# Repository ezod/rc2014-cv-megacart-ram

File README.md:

# RC2014 ColecoVision MegaCart 32KB/512KB RAM Module

This is a RAM module for [RC2014](https://rc2014.co.uk/) computers designed to provide bank-switching compatible with Opcode Games' [MegaCart](https://forums.atariage.com/topic/216354-colecovision-megacart-faq/). With the provided loader, both ordinary ColecoVision ROMs and MegaCart ROMs up to 512KB can be run from memory.

## How It Works

The module is essentially a drop-in replacement for a standard [RC2014 64k RAM](https://rc2014.co.uk/modules/64k-ram/) module configured to use the full 64KB address space.

The lower 32KB works exactly as in the standard module, including the page pin.

Initially on power-up, the upper 32KB also works exactly as in the standard module. However, upper memory actually uses a 512KB RAM, which is divided into 32 16KB banks. Bank switching can be toggled for either the lower 16KB or the upper 16KB by writing to a register on a configurable I/O port. Writing a 0 or 1 in D0 or D1 disables or enables bank switching on the lower 16KB or the upper 16KB, respectively. In other words, 0 disables bank switching, 1 enables it for the lower 16KB, and 2 enables it for the upper 16KB. (It is technically possible to enable bank switching for both ranges, but they will then both point at the same bank.) Writing a 1 in D2, D3, or D4 forces A16, A17, or A18 high, respectively, allowing the bank mirroring to work as in the 64KB/128KB/256KB MegaCarts for compatibility with those ROMs.

The register values actually used by the loader program in this repository are:

| Value | Bank Switching Enabled | ROM Size |
|-------|------------------------|----------|
|    0  |           no           |    any   |
|    1  |       lower 16KB       |    any   |
|    2  |       upper 16KB       |   512KB  |
|   18  |       upper 16KB       |   256KB  |
|   26  |       upper 16KB       |   128KB  |
|   30  |       upper 16KB       |    64KB  |

With bank switching enabled for one of these ranges, any read from one of the upper 32 addresses in the range (BFE0-BFFF for the lower 16KB, FFE0-FFFF for the upper 16KB) will page in the corresponding bank. By default (i.e. with bank switching disabled), for compatibility with the MegaCart, with banks numbered from 0 to 31, the lower 16KB uses bank 31, and the upper 16KB uses bank 0.

On the ColecoVision MegaCart, bank switching is always enabled on the upper 16KB (bank 0 at boot), and the lower 16KB always points at bank 31. The additional functionality of this module allows it to be used as a normal 64KB of RAM (without strange effects from unwanted bank switching), and is also necessary to keep CP/M resident in upper memory while ROM files are read from disk and loaded into the other banks.

J1 configures the write-only register I/O port to one of, from top to bottom (A0 not decoded): 0E/0F, 2E/2F, 4E/4F, 6E/6F, 8E/8F, AE/AF, CE/CF, EE/EF.

## Bill of Materials

| Reference | Part                            |
|-----------|---------------------------------|
|     U1    | AS6C62256 32K x 8 SRAM          |
|     U2    | AS6C4008 512K x 8 SRAM          |
|   U3-U4   | 74HCT273 octal D-type flip-flop |
|   U5-U6   | 74HCT21 dual 4-input AND gate   |
|   U7-U8   | 74HCT08 quad AND gate           |
|   U9-U11  | 74HCT32 quad OR gate            |
|    U12    | 74HCT02 quad NOR gate           |
|    U13    | 74HCT04 hex inverter            |
|    U14    | 74HCT138 3-to-8 line decoder    |
|   C1-C14  | 0.1uF disc/MLCC capacitor       |
|     J1    | 2x8 straight pin header         |
|    BUS    | 2x40 right angle pin header     |

## Building a RC2014 ColecoVision

Your RC2014 will need several other modules and some specific configuration to run ColecoVision games.

### TMS9918 Video Card

The ColecoVision uses the [TMS9918 VDP](https://en.wikipedia.org/wiki/TMS9918) for graphics. J. B. Langston's [TMS9918A video card](https://github.com/jblang/TMS9918A) for the RC2014 can be configured to respond to the A0-BF address range and send its interrupt signal to NMI, for compatibility with unmodified ColecoVision software.

Unfortunately, although the standard RC2014 [Pageable ROM](https://rc2014.co.uk/modules/pageable-rom/) module canonically uses ports 30 and 38, it conflicts with the B0-BF range needed by the VDP. It is possible to [modify the module](https://github.com/jblang/TMS9918A/issues/12) to reduce the address range to 30-3F.

### SN76489 Sound Card

The ColecoVision uses the [SN76489](https://en.wikipedia.org/wiki/Texas_Instruments_SN76489) sound generator for music and sound effects. J. B. Langston's [SN76489 sound card](https://github.com/jblang/SN76489) for the RC2014 can be configured to respond to port FF, for compatibility with unmodified ColecoVision software.

### AY-3-8910/YM2149F Sound Card

Many modern ColecoVision releases depend on Opcode Games' [Super Game Module](https://www.colecovision.dk/sem.htm). In addition to expanded RAM, the SGM includes an AY-3-8910 sound generator for enhanced sound and music. Ed Brindley's [YM2149F sound card](https://github.com/electrified/rc2014-ym2149) for the RC2014 can be configured to use ports 50, 51, and 52 for register select, write, and read, respectively, for compatibility with unmodified ColecoVision SGM software.

### Controller Interface

J. B. Langston's [game controller interface](https://github.com/jblang/GameController) for the RC2014 works with original ColecoVision controllers (or compatible controllers), and works with unmodified ColecoVision software.

### Clock

The Z80 CPU in the ColecoVision is driven by a 3.579545 MHz main clock. Dividing Clock 1 by 2 on the standard [Dual Clock](https://rc2014.co.uk/modules/dual-clock-module/) module sets the main clock speed to 3.6864 MHz, which is fairly close and seems to work with most (all?) games. Alternatively, an actual 3.579545 MHz oscillator can be connected to the external clock interface.

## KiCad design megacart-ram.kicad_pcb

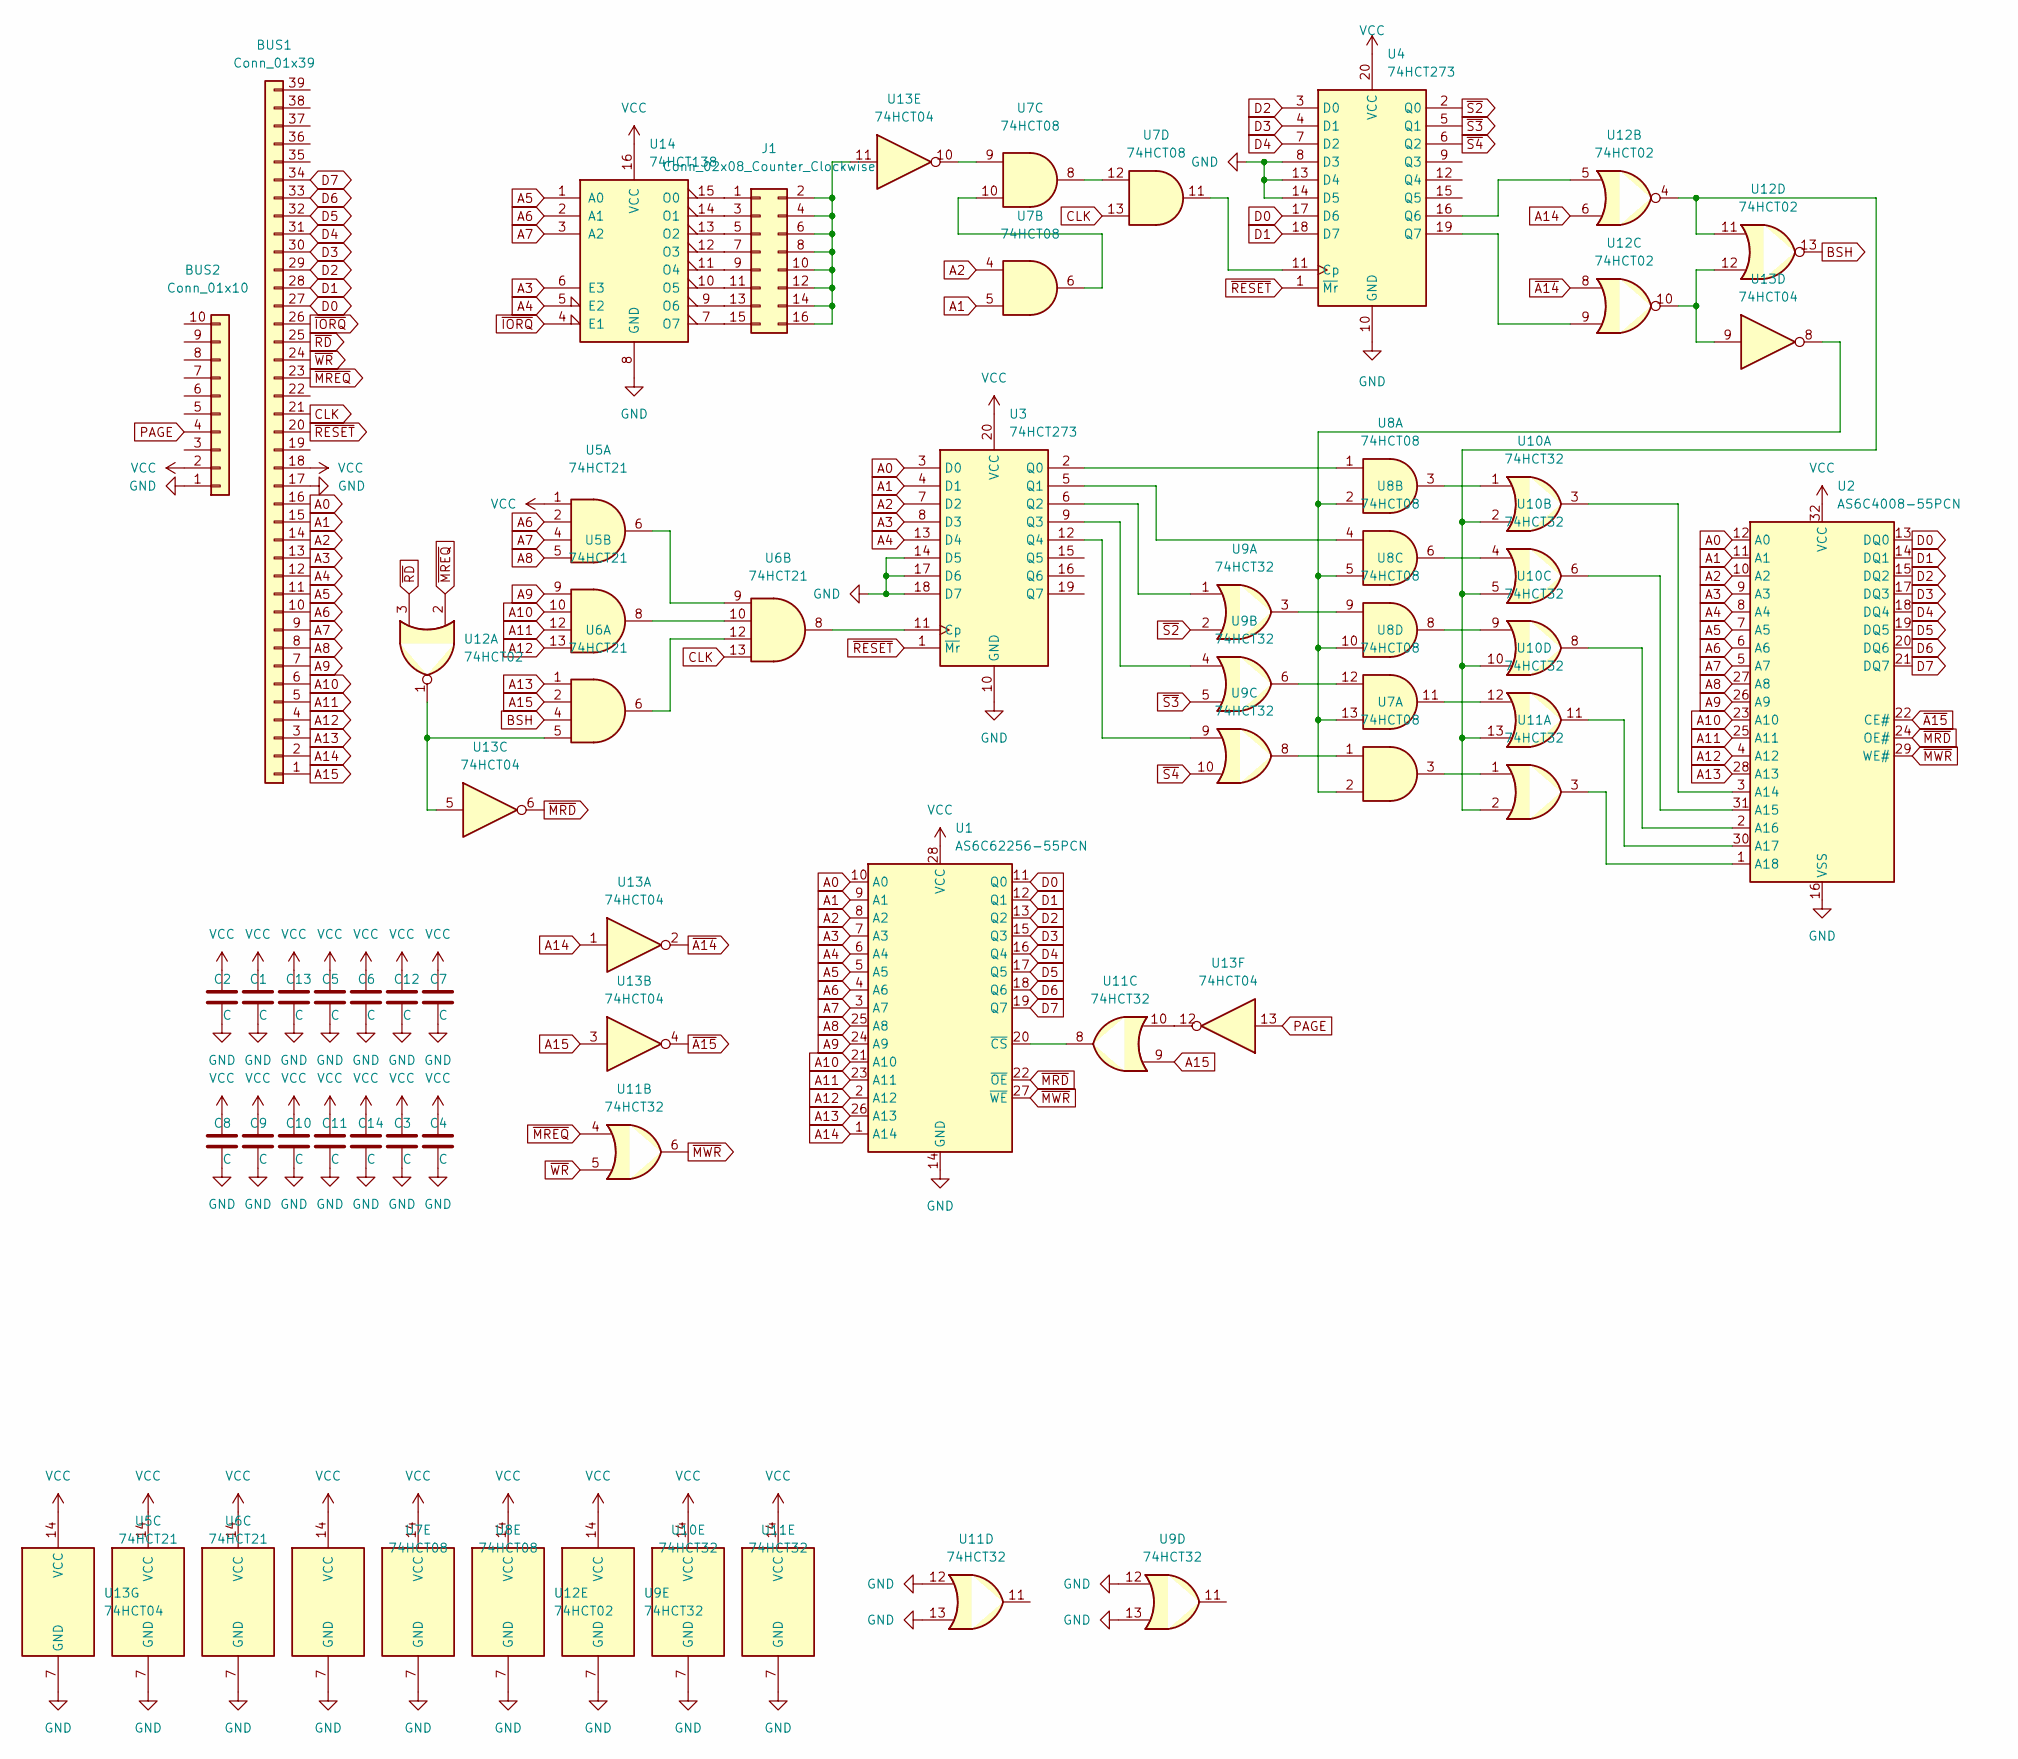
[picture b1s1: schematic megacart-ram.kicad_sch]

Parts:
BUS1: Conn_01x39; PinHeader_1x39_P2.54mm_Vertical
BUS2: Conn_01x10; PinHeader_1x10_P2.54mm_Vertical
C1, C2, C3, C4, C5, C6, C7, C8, C9, C10, C11, C12, C13, C14: C; C_Disc_D5.0mm_W2.5mm_P2.50mm
J1: Conn_02x08_Counter_Clockwise; PinHeader_2x08_P2.54mm_Vertical
U1: AS6C62256-55PCN; DIP-28_W15.24mm
U2: AS6C4008-55PCN; DIP-32_W15.24mm
U3, U4: 74HCT273; DIP-20_W7.62mm
U5, U6: 74HCT21; DIP-14_W7.62mm
U7, U8: 74HCT08; DIP-14_W7.62mm
U9, U10, U11: 74HCT32; DIP-14_W7.62mm
U12: 74HCT02; DIP-14_W7.62mm
U13: 74HCT04; DIP-14_W7.62mm
U14: 74HCT138; DIP-16_W7.62mm

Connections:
A0: BUS1.16, U1.10 (A0), U2.12 (A0), U3.3 (D0)
A1: BUS1.15, U1.9 (A1), U2.11 (A1), U3.4 (D1), U7.5
A2: BUS1.14, U1.8 (A2), U2.10 (A2), U3.7 (D2), U7.4
A3: BUS1.13, U1.7 (A3), U2.9 (A3), U3.8 (D3), U14.6 (E3)
A4: BUS1.12, U1.6 (A4), U2.8 (A4), U3.13 (D4), U14.5 (E2)
A5: BUS1.11, U1.5 (A5), U2.7 (A5), U14.1 (A0)
A6: BUS1.10, U1.4 (A6), U2.6 (A6), U5.2, U14.2 (A1)
A7: BUS1.9, U1.3 (A7), U2.5 (A7), U5.4, U14.3 (A2)
A8: BUS1.8, U1.25 (A8), U2.27 (A8), U5.5
A9: BUS1.7, U1.24 (A9), U2.26 (A9), U5.9
A10: BUS1.6, U1.21 (A10), U2.23 (A10), U5.10
A11: BUS1.5, U1.23 (A11), U2.25 (A11), U5.12
A12: BUS1.4, U1.2 (A12), U2.4 (A12), U5.13
A13: BUS1.3, U1.26 (A13), U2.28 (A13), U6.1
A14: BUS1.2, U1.1 (A14), U12.6, U13.1
A15: BUS1.1, U6.2, U11.9, U13.3
BSH: U6.4, U12.13
CLK: BUS1.21, U6.13, U7.13
D0: BUS1.27, U1.11 (Q0), U2.13 (DQ0), U4.17 (D6)
D1: BUS1.28, U1.12 (Q1), U2.14 (DQ1), U4.18 (D7)
D2: BUS1.29, U1.13 (Q2), U2.15 (DQ2), U4.3 (D0)
D3: BUS1.30, U1.15 (Q3), U2.17 (DQ3), U4.4 (D1)
D4: BUS1.31, U1.16 (Q4), U2.18 (DQ4), U4.7 (D2)
D5: BUS1.32, U1.17 (Q5), U2.19 (DQ5)
D6: BUS1.33, U1.18 (Q6), U2.20 (DQ6)
D7: BUS1.34, U1.19 (Q7), U2.21 (DQ7)
GND: BUS1.17, BUS2.1, C1.2, C2.2, C3.2, C4.2, C5.2, C6.2, C7.2, C8.2, C9.2, C10.2, C11.2, C12.2, C13.2, C14.2, U1.14 (GND), U2.16 (VSS), U3.10 (GND), U3.14 (D5), U3.17 (D6), U3.18 (D7), U4.8 (D3), U4.10 (GND), U4.13 (D4), U4.14 (D5), U5.7 (GND), U6.7 (GND), U7.7 (GND), U8.7 (GND), U9.7 (GND), U9.12, U9.13, U10.7 (GND), U11.7 (GND), U11.12, U11.13, U12.7 (GND), U13.7 (GND), U14.8 (GND)
unnamed: J1.1, U14.15 (O0)
unnamed: J1.3, U14.14 (O1)
unnamed: J1.5, U14.13 (O2)
unnamed: J1.7, U14.12 (O3)
unnamed: J1.9, U14.11 (O4)
unnamed: J1.2, J1.4, J1.6, J1.8, J1.10, J1.12, J1.14, J1.16, U13.11
unnamed: J1.11, U14.10 (O5)
unnamed: J1.13, U14.9 (O6)
unnamed: J1.15, U14.7 (O7)
unnamed: U2.1 (A18), U11.3
unnamed: U2.2 (A16), U10.8
unnamed: U2.3 (A14), U10.3
unnamed: U2.30 (A17), U10.11
unnamed: U2.31 (A15), U10.6
unnamed: U3.2 (Q0), U8.1
unnamed: U3.5 (Q1), U8.4
unnamed: U3.6 (Q2), U9.1
unnamed: U3.9 (Q3), U9.4
unnamed: U3.11 (Cp), U6.8
unnamed: U3.12 (Q4), U9.9
unnamed: U4.11 (Cp), U7.11
unnamed: U4.16 (Q6), U12.5
unnamed: U4.19 (Q7), U12.9
unnamed: U5.6, U6.9
unnamed: U5.8, U6.10
unnamed: U6.6, U6.12
unnamed: U7.1, U9.8
unnamed: U7.6, U7.10
unnamed: U7.8, U7.12
unnamed: U8.9, U9.3
unnamed: U8.12, U9.6
unnamed: U8.3, U10.1
unnamed: U8.6, U10.4
unnamed: U8.8, U10.9
unnamed: U10.2, U10.5, U10.10, U10.13, U11.2, U12.4, U12.11
unnamed: U8.11, U10.12
unnamed: U7.3, U11.1
unnamed: U1.20 (~CS), U11.8
unnamed: U11.10, U13.12
unnamed: U6.5, U12.1, U13.5
unnamed: U7.2, U8.2, U8.5, U8.10, U8.13, U13.8
unnamed: U12.10, U12.12, U13.9
unnamed: U7.9, U13.10
PAGE: BUS2.4, U13.13
VCC: BUS1.18, BUS2.2, C1.1, C2.1, C3.1, C4.1, C5.1, C6.1, C7.1, C8.1, C9.1, C10.1, C11.1, C12.1, C13.1, C14.1, U1.28 (VCC), U2.32 (VCC), U3.20 (VCC), U4.20 (VCC), U5.1, U5.14 (VCC), U6.14 (VCC), U7.14 (VCC), U8.14 (VCC), U9.14 (VCC), U10.14 (VCC), U11.14 (VCC), U12.14 (VCC), U13.14 (VCC), U14.16 (VCC)
~A14: U12.8, U13.2
~A15: U2.22 (CE#), U13.4
~IORQ: BUS1.26, U14.4 (E1)
~MRD: U1.22 (~OE), U2.24 (OE#), U13.6
~MREQ: BUS1.23, U11.4, U12.2
~MWR: U1.27 (~WE), U2.29 (WE#), U11.6
~RD: BUS1.25, U12.3
~RESET: BUS1.20, U3.1 (~Mr), U4.1 (~Mr)
~S2: U4.2 (Q0), U9.2
~S3: U4.5 (Q1), U9.5
~S4: U4.6 (Q2), U9.10
~WR: BUS1.24, U11.5

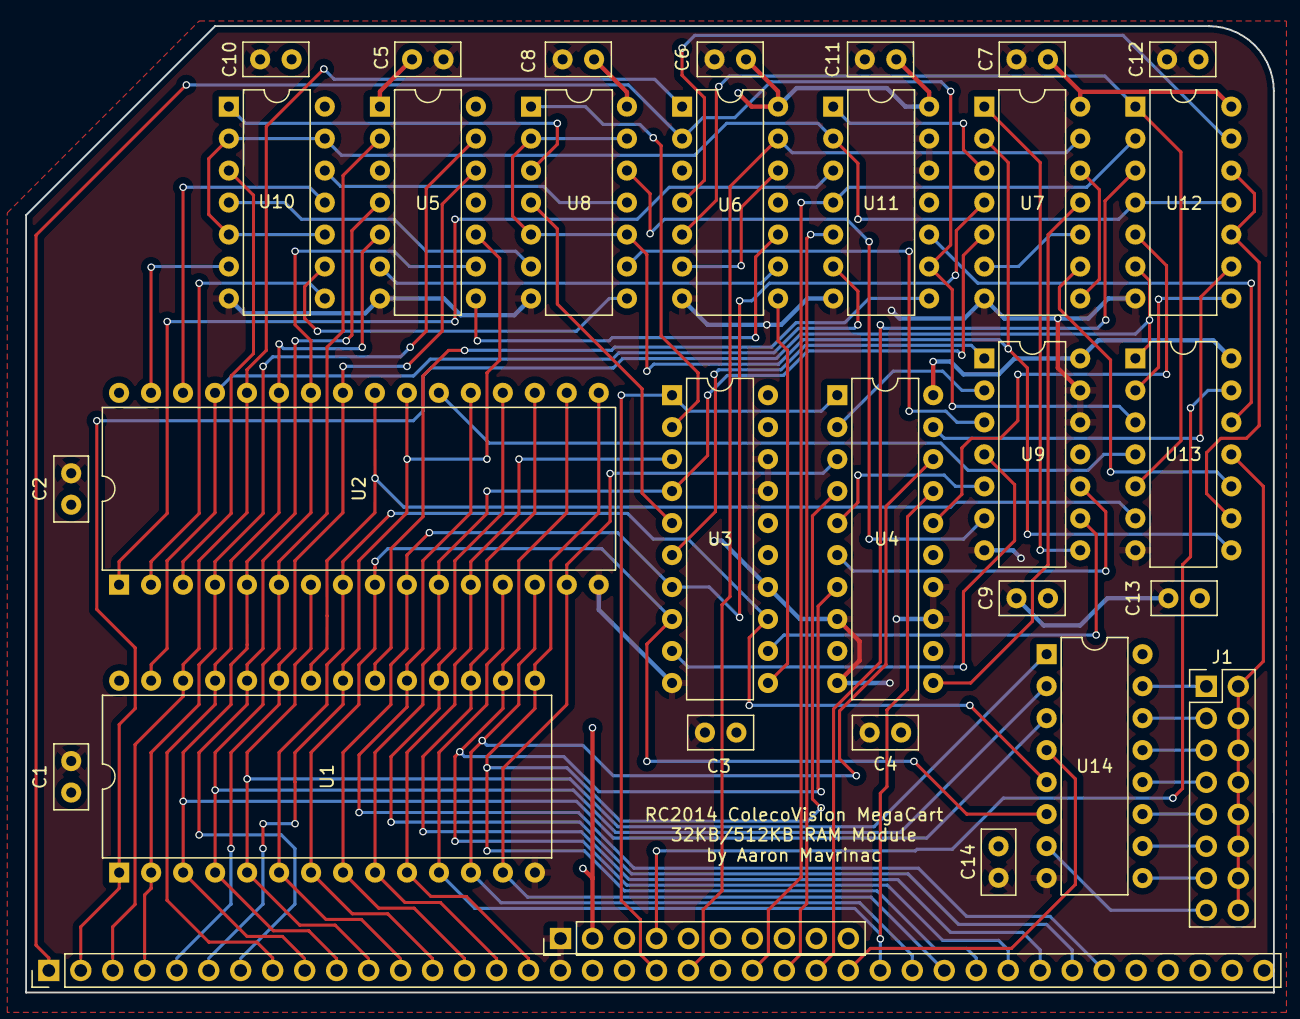
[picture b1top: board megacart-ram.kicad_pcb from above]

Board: 2 copper layers, 99.1 x 76.8 mm, 31 parts (0 on the bottom side), 84 nets.

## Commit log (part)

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2024-01-22 Initial import of loader.asm.
2024-01-23 Add MegaCart loading code.
2024-01-23 Add .gitignore.
2024-01-23 Limit MegaCart reads to 16KB chunks.
2024-01-23 Convert loader.asm to UNIX format.
2024-01-24 Distinguish lower and upper slot select memory locations.
2024-01-25 Open file first, increase verbosity.
2024-01-25 Remove unnecessary op.
2024-01-25 Use proper slot offset for upper bank.
2024-01-25 Verify magic number.
2024-01-25 Use single-byte read to set slot.
2024-01-25 Rearrange loading logic.
2024-01-31 Rename SLOT0 and SLOTF to be less confusing.
2024-01-31 Move the BIOS loading code after the BIOS, so the jump to BOOT completes.
2024-01-31 Load compiled code memory instead of individual opcodes.
2024-02-01 Move loader into software subdirectory.
2024-02-01 Ignore .com files.
2024-02-01 Add test programs.
2024-02-01 Initial commit of MegaCart RAM board KiCAD project.
2024-02-01 Clean up schematic.
2024-02-01 Add decoupling caps and update PCB with RC2014 template.
2024-02-01 Ignore autosave files.
2024-02-01 Add explicit power units for 7400 ICs.
2024-02-03 Ignore -bak files.
2024-02-03 First pass at routing PCB.
2024-02-05 Routing optimizations.
2024-02-05 Ignore _autosave files.
2024-02-05 Finalize PCB design.
2024-02-05 Generate gerbers with JLCPCB specs.
2024-02-05 Remove spurious round marker.
2024-02-06 Initial README.
2024-02-06 Add part descriptions to BOM.
2024-02-06 Improve functional documentation.
2024-03-01 Add image of PCB.
2024-03-01 New backward-compatible loader for improved module.
2024-03-01 Simplify MegaCart size-based bank mirroring.
2024-03-05 Updated revision of PCB supporting bank mirroring for 64/128/256K MegaCarts.
2024-03-05 Renumber some components.
2024-03-05 Update Gerbers.
2024-03-05 Add PDF export of schematic.
2024-03-05 Reorder capacitors by number.
2024-03-06 Add documentation about address line override register bits.
2024-03-30 Update PCB photo.
2025-01-03 Fix tab spacing in assembly sources.
2025-01-03 Convert tabs to spaces for consistency.
2025-06-06 Add SID dump player program.
2025-06-06 Add slot progress characters to play loop.
2025-06-06 Simplify slot initialization and fix slot boundary check.
2025-06-06 Simplify bank switch, remove bank switch dot, and increase playback speed.
2025-06-06 Convert to use new bitfield-delta compressed format.
2025-06-06 Fix EOF detection logic.
2025-06-06 Improve EOF check to handle incorrect files.
2025-06-06 Push q to quit during playback.
2025-06-09 Add track information printing and document file format.
2025-06-09 Apply various optimizations.
2025-06-09 Fix silence iteration.
